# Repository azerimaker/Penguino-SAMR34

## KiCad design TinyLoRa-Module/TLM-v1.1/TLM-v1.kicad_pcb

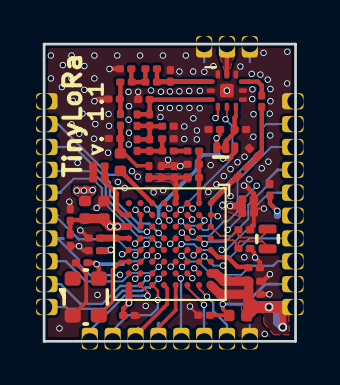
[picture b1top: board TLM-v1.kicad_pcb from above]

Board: 4 copper layers, 14.0 x 16.5 mm, 54 parts (0 on the bottom side), 52 nets.

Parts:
C1: 10uF; C_0402_1005Metric
C2, C3, C4, C5, C6, C8, C9, C10, C11, C13, C14, C15, C35: 100nF; C_0201_0603Metric
C7: 33pF; C_0201_0603Metric
C12, C33: 4.7pF; C_0201_0603Metric
C16, C24, C26, C27: DNM; C_0201_0603Metric
C17: 18pF; C_0201_0603Metric
C18, C29: 3.9pF; C_0201_0603Metric
C19, C21, C32: 3.3pF; C_0201_0603Metric
C20, C31: 5.6pF; C_0201_0603Metric
C22: 47pF; C_0201_0603Metric
C23: 2.7pF; C_0201_0603Metric
C25: 4.7nF; C_0201_0603Metric
C28: 22pF; C_0201_0603Metric
C30: 8.2pF; C_0201_0603Metric
C34: 1nF; C_0201_0603Metric
C36, C37: 10pF; C_0201_0603Metric
FB1: BLM15AG121SN1D; L_0402_1005Metric
JP1: RFSW_VCC_SLCT; JP_NO_NC
L3: 2.2nH; L_0402_1005Metric
L4, L5, L7, L10, L11: 10nH; L_0201_0603Metric
L6, L8: 33nH; L_0201_0603Metric
L9: 11nH; L_0201_0603Metric
R1: 100K; R_0402_1005Metric
U1: TLM01; TLM-01-module
U2: ATSAMR34J18B; TFBGA-64_6.0x6.0mm_Layout8x8_P0.65mm
U3: SKY13373-460LF; QFN-12-1EP_3x3mm_P0.5mm_EP1.65x1.65mm
XC1: TYETBCSANF-32.000000; Oscilator_2.5x2.0
Y1: ABS05-32.768KHZ-9-T; ABS05_32.768KHz Crystal

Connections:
+BATT: C33.1, U1.23, U2.C3
ANT_PAD: U1.30, U3.11
BAND_SEL: U2.F6, U3.4
GND: C1.2, C2.2, C3.2, C4.1, C5.2, C6.2, C7.2, C8.2, C9.2, C10.2, C11.2, C12.2, C13.1, C14.2, C15.2, C18.2, C19.2, C20.2, C21.2, C23.2, C24.2, C25.2, C29.2, C30.2, C31.2, C32.2, C33.2, C34.2, C35.2, C36.2, C37.2, U1.1, U1.18, U1.28, U1.29, U1.31, U2.A2, U2.B2, U2.B3, U2.B5, U2.B7, U2.D4, U2.D6, U2.E1, U2.E2, U2.F2, U2.G2, U2.G3, U2.G5, U2.G6, U2.G7, U2.H5, U3.2, U3.7, U3.8, U3.10, U3.12, U3.13, XC1.2
unnamed: C7.1, C8.1, U2.H2
unnamed: C9.1, U2.H4
unnamed: C14.1, U2.A5
unnamed: C16.1, C21.1, L5.2, U3.1
unnamed: C16.2, C20.1, L4.2, L5.1
unnamed: C17.1, C19.1, L4.1
unnamed: C17.2, C18.1, L3.2, L6.1
unnamed: C22.1, C23.1, L7.1
unnamed: C22.2, U3.9
unnamed: C26.1, C27.2, C31.1, L10.2, L11.1
unnamed: C26.2, C30.1, L9.2, L10.1
unnamed: C27.1, C32.1, L11.2, U3.3
unnamed: C28.1, L9.1
unnamed: C34.1, JP1.2, U3.6
PA04_S0_UART_TX: U1.27, U2.D3
PA05_S0_UART_RX: U1.26, U2.C4
PA06_ADC6: JP1.3, U1.2, U2.E3
PA07_ADC7: U1.4, U2.F3
PA08_GPIO: U1.6, U2.F4
PA14_GPIO: U1.12, U2.F8
PA15_GPIO: U1.11, U2.G8
PA16_S1_I2C_SDA: U1.9, U2.F7
PA17_S1_I2C_SCL: U1.8, U2.E6
PA18_PWM_T0_W2: U1.10, U2.E7
PA19_PWM_T0_W3: U1.13, U2.E8
PA22_GPIO: U1.14, U2.D8
PA23_S5_SPI_SS: U1.15, U2.D7
PA27_GPIO: U1.3, U2.E4
PA28_GPIO: U1.24, U2.C6
PA30_SWDCLK: U1.21, U2.C5
PA31_SWDIO: U1.22, U2.D5
PA_BOOST: L3.1, U2.F1
PB02_S5_SPI_MISO: U1.25, U2.B4
PB22_S5_SPI_MOSI: U1.5, U2.E5
PB23_S5_SPI_SCK: U1.7, U2.C7
RFI_HF: L7.2, U2.A1
RFO_HF: C28.2, C29.1, L8.2, U2.B1
TCXO_PWR: C35.1, U2.F5, XC1.4
TXRX_RF: U2.D2, U3.5
USB_N: U1.17, U2.B8
USB_P: U1.16, U2.C8
VDD: C3.1, C4.2, C5.1, C13.2, FB1.2, R1.1, U1.19, U2.A7, U2.A8, U2.G4, U2.H8
VDDA: C1.1, C2.1, C6.1, C10.1, C11.1, C12.1, FB1.1, JP1.1, U2.C1, U2.C2, U2.H3
VR_PA: C24.1, C25.1, L6.2, L8.1, U2.D1
XIN32: C36.1, U2.A3, Y1.1
XOUT32: C37.1, U2.A4, Y1.2
XTA: U2.H6, XC1.3
~RESET: C15.1, R1.2, U1.20, U2.B6
